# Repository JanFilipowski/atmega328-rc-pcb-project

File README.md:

# ATmega328 RC PCB Project

A custom KiCad hardware design for an ATmega328-based RC electronics board.

## Project Overview

This repository contains the complete KiCad design files for a PCB built around the ATmega328 microcontroller.
It includes schematic, board layout, project settings, and backup snapshots.

## Preview

## Repository Contents

- `ATMEGA328ip.pcb.kicad_sch` - Main schematic file.
- `ATMEGA328ip.pcb.kicad_pcb` - PCB layout.
- `ATMEGA328ip.pcb.kicad_pro` - KiCad project definition.
- `ATMEGA328ip.pcb.kicad_prl` - Local project settings.
- `ATMEGA328ip.pcb-backups/` - Automatic backup copies.

## Requirements

- KiCad 6.x or newer (recommended: KiCad 7/8).

## How To Open The Project

1. Start KiCad.
2. Open `ATMEGA328ip.pcb.kicad_pro`.
3. Use **Schematic Editor** to inspect the circuit.
4. Use **PCB Editor** to inspect traces, footprints, and board outline.

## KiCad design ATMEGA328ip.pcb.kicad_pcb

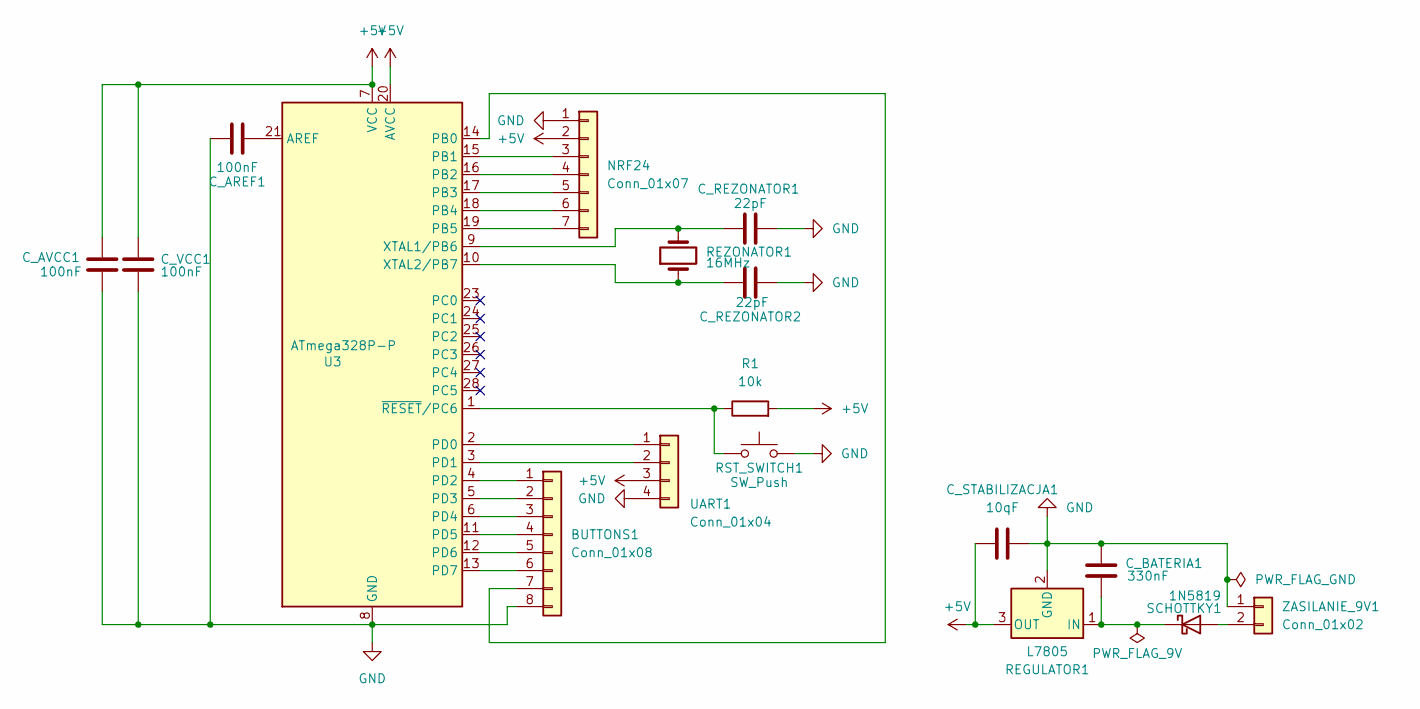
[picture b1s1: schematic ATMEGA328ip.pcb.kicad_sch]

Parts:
BUTTONS1: Conn_01x08; PinHeader_1x08_P2.54mm_Vertical
C_AREF1: 100nF; C_Disc_D5.0mm_W2.5mm_P5.00mm
C_AVCC1: 100nF; C_Disc_D5.0mm_W2.5mm_P5.00mm
C_BATERIA1: 330nF; C_Disc_D5.0mm_W2.5mm_P5.00mm
C_REZONATOR1, C_REZONATOR2: 22pF; C_Disc_D5.0mm_W2.5mm_P5.00mm
C_STABILIZACJA1: 10qF; C_Disc_D5.0mm_W2.5mm_P5.00mm
C_VCC1: 100nF; C_Disc_D5.0mm_W2.5mm_P5.00mm
NRF24: Conn_01x07; PinSocket_1x07_P2.54mm_Vertical
R1: 10k; R_Axial_DIN0207_L6.3mm_D2.5mm_P10.16mm_Horizontal
REGULATOR1: L7805; TO-220-3_Vertical
REZONATOR1: 16MHz; Crystal_HC49-U_Vertical
RST_SWITCH1: SW_Push; SW_PUSH-12mm_Wuerth-430476085716
SCHOTTKY1: 1N5819; D_DO-41_SOD81_P10.16mm_Horizontal
U3: ATmega328P-P; DIP-28_W7.62mm_Socket
UART1: Conn_01x04; PinSocket_1x04_P2.54mm_Vertical
ZASILANIE_9V1: Conn_01x02; PinSocket_1x02_P2.54mm_Vertical

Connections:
+5V: C_AVCC1.1, C_STABILIZACJA1.1, C_VCC1.1, NRF24.2, R1.2, REGULATOR1.3 (OUT), U3.7 (VCC), U3.20 (AVCC), UART1.3
GND: BUTTONS1.8, C_AREF1.1, C_AVCC1.2, C_BATERIA1.1, C_REZONATOR1.2, C_REZONATOR2.2, C_STABILIZACJA1.2, C_VCC1.2, NRF24.1, REGULATOR1.2 (GND), RST_SWITCH1.2, U3.8 (GND), U3.22 (GND), UART1.4, ZASILANIE_9V1.1
unnamed: BUTTONS1.1, U3.4 (PD2)
unnamed: BUTTONS1.2, U3.5 (PD3)
unnamed: BUTTONS1.3, U3.6 (PD4)
unnamed: BUTTONS1.4, U3.11 (PD5)
unnamed: BUTTONS1.5, U3.12 (PD6)
unnamed: BUTTONS1.6, U3.13 (PD7)
unnamed: BUTTONS1.7, U3.14 (PB0)
unnamed: NRF24.3, U3.15 (PB1)
unnamed: NRF24.4, U3.16 (PB2)
unnamed: NRF24.5, U3.17 (PB3)
unnamed: NRF24.6, U3.18 (PB4)
unnamed: NRF24.7, U3.19 (PB5)
unnamed: C_BATERIA1.2, REGULATOR1.1 (IN), SCHOTTKY1.1 (K)
unnamed: SCHOTTKY1.2 (A), ZASILANIE_9V1.2
unnamed: C_AREF1.2, U3.21 (AREF)
unnamed: U3.2 (PD0), UART1.1
unnamed: U3.3 (PD1), UART1.2
unnamed: C_REZONATOR1.1, REZONATOR1.2, U3.9 (XTAL1/PB6)
unnamed: C_REZONATOR2.1, REZONATOR1.1, U3.10 (XTAL2/PB7)
unnamed: R1.1, RST_SWITCH1.1, U3.1 (~RESET/PC6)

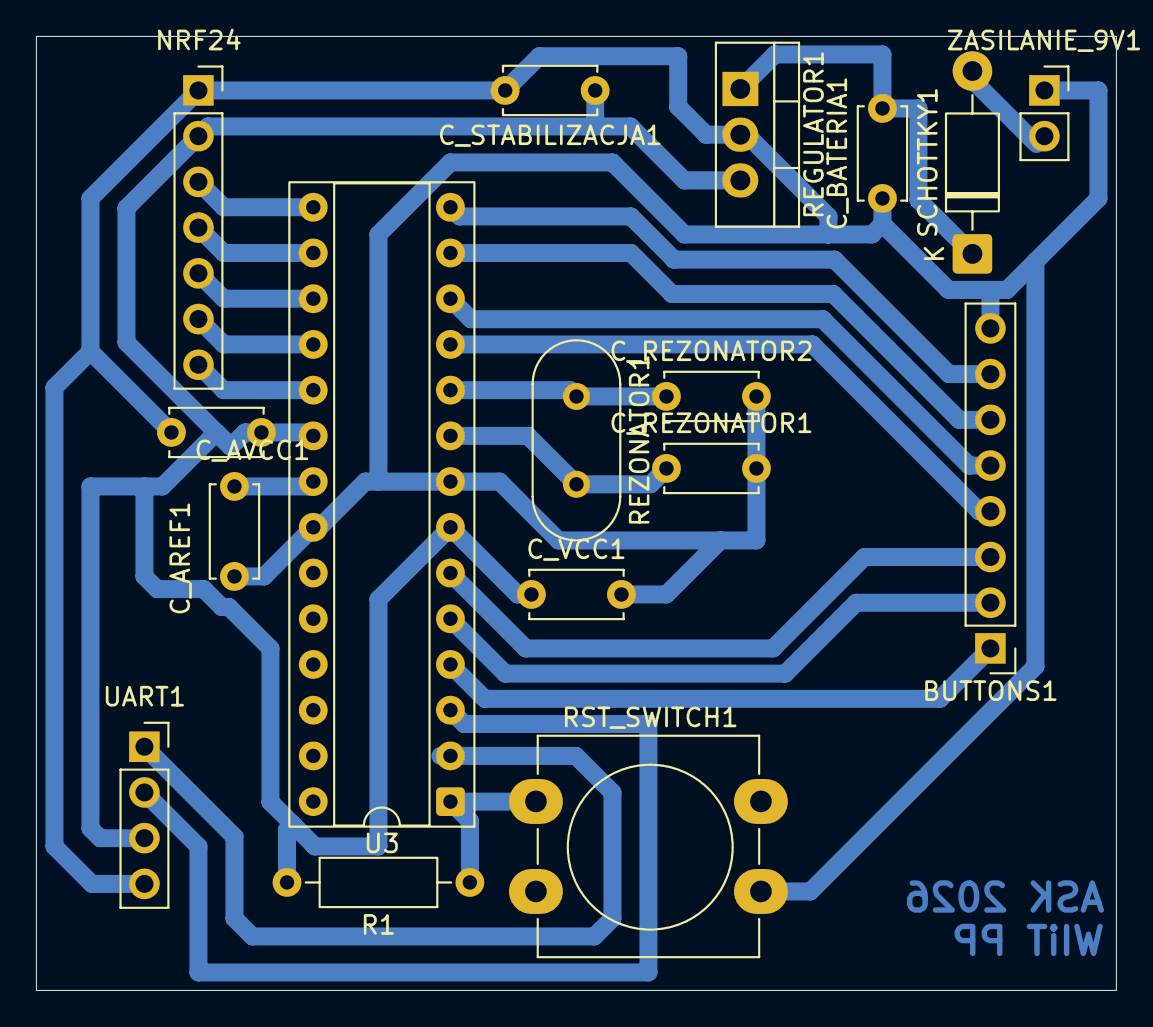
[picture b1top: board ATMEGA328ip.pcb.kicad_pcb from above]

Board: 2 copper layers, 60.0 x 53.0 mm, 17 parts (0 on the bottom side), 22 nets.

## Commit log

2026-04-26 full płytka
2026-04-27 readme update
